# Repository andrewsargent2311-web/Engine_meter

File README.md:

# Engine Meter (RPMuffin)

A small, battery-powered engine monitor for a paramotor. It measures **RPM**, **CHT** and **EGT**, and sends them over **Bluetooth LE** as NMEA-style sentences to [Gaggle](https://www.gaggle.aero/) or the `paraglide_vario_ESP32` flight computer. It also reports its own battery percentage.

It was designed and tested on a **Moster 185** (single-cylinder two-stroke), but it should work on any engine with a spark-ignition lead and a thermocouple-instrumented head or exhaust.

| | |
|---|---|
| **MCU** | nice!nano (nRF52840) |
| **RPM** | Inductive pickup (2 wraps on the HT lead) → LMV331 comparator → interrupt |
| **Temperature** | 2 × MAX31856 thermocouple amplifiers (CHT + EGT), K-type as shipped |
| **Radio** | BLE, Nordic UART Service, advertises as `ParaEngineMeter` |
| **Update rate** | 5 Hz |
| **Power** | 1000 mAh single-cell LiPo, JST-PH 2.0 mm, charged over USB-C |
| **PCB** | 2 layers, 1.6 mm, about 50.6 × 75.1 mm |
| **Case** | 3D printed (PLA), about 58.5 × 123.5 × 27 mm including mounting tabs |

---

## Repository layout

| Path | Contents |
|---|---|
| `Engine_meter/` | PlatformIO firmware project (open **this** folder in VS Code) |
| `Engine_meter/src/` | `main.cpp` (RPM, thermocouples, BLE) and `AuxSensors.cpp/.h` (battery gauge) |
| `Engine_meter/boards/` | Custom `nicenano` board definition and pin variant for PlatformIO |
| `Engine_monitor_V1/` | KiCad 10 project: schematic and PCB |
| `Engine_monitor_V1/Gerber files/` | Fabrication outputs: Gerbers, drill files, JLCPCB BOM, JLCPCB CPL, and `Engine_monitor_V1_order.zip` |
| `3D print files/` | Case and lid as STL, plus ready-sliced G-code for a Prusa MK3S |
| `Photos/` | Photos of the bare PCB and the finished unit |

---

## 1. Parts list

### Parts on the PCB (SMD, 0805 unless noted)

These are the parts in `Engine_monitor_V1_BOM_JLCPCB.xlsx`, and they can be assembled by JLCPCB.

| Qty | Value | Designators | Notes |
|---|---|---|---|
| 4 | 10 nF 50 V X7R | C1, C3, C9, C10 | Thermocouple input filtering |
| 7 | 100 nF 50 V X7R | C2, C4, C5, C8, C11, C12, C14 | Decoupling; C8 filters the comparator reference |
| 2 | 10 µF 25 V X5R | C6, C13 | 3.3 V bulk decoupling |
| 4 | 100 Ω 1 % | R1, R2, R11, R12 | Thermocouple input series resistors |
| 5 | 10 kΩ 1 % | R4, R5, R7, R8, R9 | R4/R5 chip-select pull-ups, R7/R8 comparator reference divider, R9 comparator output pull-up |
| 1 | **150 kΩ** 1 % | R10 | RPM input series resistor. See the note below |
| 1 | 1 MΩ 1 % | R13 | Comparator hysteresis (positive feedback) |
| 1 | 220 kΩ 1 % | R14 | RPM input divider to GND |
| 2 | 1N5819HW-7-F Schottky, SOD-123 | D9, D10 | RPM input clamps (to 3.3 V and to GND) |
| 1 | LMV331IDBVR, SOT-23-5 | U2 | Single comparator |
| 2 | MAX31856MUD+, TSSOP-14 | U3, U4 | U3 = **CHT**, U4 = **EGT** |

> **R10 value:** the production design uses **150 kΩ**. It was originally 22 kΩ, which was too sensitive to pick up noise on the ignition lead, so it was increased. Use 150 kΩ.
>
> **D9/D10 in the JLCPCB BOM** are marked "consigned" (you supply them). Either supply 1N5819HW-7-F parts yourself, or pick an in-stock SOD-123 Schottky at order time.

### Parts you add by hand (through-hole / modules)

| Ref | Part | Purpose |
|---|---|---|
| U1 | **nice!nano** (v2 or compatible, nRF52840), 2 × 12-pin headers or castellated solder | MCU, BLE radio, LiPo charger |
| BT1 | JST-PH 2.0 mm 2-pin horizontal header (S2B-PH-K) | Battery connector |
| J2 | 2-pin screw terminal, 3.81 mm pitch (Phoenix MC 1,5/2-G-3.81 footprint) | **Power switch** (in series with the battery) |
| X1 | 2-pin screw terminal, 3.5 mm pitch | **CHT** thermocouple input |
| X2 | 2-pin screw terminal, 3.5 mm pitch | **EGT** thermocouple input |
| J1 | 1-pin 2.54 mm header (or a wire soldered straight in) | RPM pickup input |

### Other items

- **Battery:** 1000 mAh single-cell LiPo with a **2 mm JST-PH** connector (ideally with a built-in protection circuit).
- **Power switch:** any small SPST switch rated for a few hundred mA, wired to J2.
- **Thermocouples:** two K-type probes, one for CHT (for example a spark-plug washer or bolt-on type) and one for EGT (exhaust probe). Use proper thermocouple wire or a compensated extension.
- **RPM pickup wire:** a short length of insulated hookup wire.
- **Fasteners:** 4 small self-tapping screws for the lid (see section 5), plus zip ties or straps for mounting.
- USB-C cable for programming and charging.

---

## 2. Order and build the PCB

1. Go to JLCPCB and upload `Engine_monitor_V1/Gerber files/Engine_monitor_V1_order.zip`.
2. Settings: **2 layers, 1.6 mm** thickness. The board is about 50.6 × 75.1 mm.
3. **Bare board:** order the PCB only and hand-solder everything.
4. **Assembled:** tick *PCB Assembly*, then upload `Engine_monitor_V1_BOM_JLCPCB.xlsx` and `Engine_monitor_V1_CPL_JLCPCB.csv`. The BOM has no LCSC part numbers, so match each line to a stocked part in the JLCPCB parts picker (see the part table above). Only the SMD parts on the top side are assembled. You add the nice!nano, terminals, header and JST connector yourself.

### Hand-soldering order (if building from a bare board)

The two MAX31856 chips are TSSOP-14, so the SMD parts are best done with flux, a fine tip and a magnifier.

1. U2, U3, U4 (the ICs). Check pin 1 orientation against the silkscreen.
2. The 0805 resistors and capacitors, then the two diodes D9/D10 (check the stripe against the silkscreen).
3. Terminal blocks X1, X2, J2 and the JST connector BT1.
4. J1.
5. Finally the nice!nano. Either solder header pins or solder it directly. Keep the USB-C end of the board towards the board edge as shown in the silkscreen.

---

## 3. How the hardware works

### Pin map

The firmware uses software (bit-banged) SPI, so the two MAX31856s share one bus with separate chip-selects.

| Signal | nice!nano GPIO | Firmware pin number |
|---|---|---|
| MAX31856 SDO → MCU (MISO) | P1.00 | 32 |
| MAX31856 SDI ← MCU (MOSI) | P1.13 | 45 |
| SCK | P1.15 | 47 |
| CS for **CHT** (U3) | P0.11 | 11 |
| CS for **EGT** (U4) | P1.04 | 36 |
| RPM comparator output | P1.11 | 43 |

Pin numbers follow the Adafruit nRF52 core convention: P0.xx → xx, P1.xx → 32 + xx.

### RPM input

- The pickup wire goes to **J1**. It passes through **R10 (150 kΩ)** into a divider with **R14 (220 kΩ)**, giving roughly 0.6 × the input voltage. **D10** clamps to GND and **D9** clamps to 3.3 V to protect the comparator.
- **U2 (LMV331)** compares that signal with a **1.65 V** reference made by R7/R8 and filtered by C8. As a rough guide, the pickup needs to swing above about **2.8 V** at J1 to trigger.
- **R13 (1 MΩ)** feeds the output back to the input for hysteresis. **R9 (10 kΩ)** pulls the open-collector output up to 3.3 V.
- The nRF52840 counts the rising edges on an interrupt.

### Thermocouple input

Each channel copies the Adafruit MAX31856 breakout design: 100 Ω series resistors on the thermocouple inputs, 10 nF / 100 nF filtering, and a 10 kΩ pull-up on each chip-select. **X1 = CHT (U3)** and **X2 = EGT (U4)**.

Polarity matters. If a reading falls when you warm the probe, swap the two wires. The firmware sets **type K** for both channels, but the MAX31856 supports B, E, J, K, N, R, S and T. To change it, edit the two `setThermocoupleType(...)` lines in `setup()` in `Engine_meter/src/main.cpp`.

### Power

- The battery connects to **BT1**. BT1 pin 1 is battery **+** and pin 2 is **GND**.
- **BT1 + goes to J2 (the switch), and the other side of the switch goes to the nice!nano's battery-in pin** (pin 26, marked BATIN/RAW on the board). So the battery is only connected to the nice!nano while the switch is **on**. Charge with the switch on.
- Charging happens through the nice!nano's USB-C port. It charges at roughly **100 mA**, so a flat 1000 mAh pack takes about **10 hours**.
- The nice!nano's regulator provides the 3.3 V rail for the comparator and both MAX31856s.

> ⚠️ **Check battery polarity before the first power-up.** JST-PH LiPo packs from different suppliers are wired in different orders, and a reversed pack can destroy the nice!nano. Use a multimeter on the pack connector, and compare it with BT1 (pin 1 = +, pin 2 = GND) on the PCB. If it is reversed, re-pin the connector on the battery lead.

---

## 4. Firmware

The firmware is a PlatformIO project in `Engine_meter/`.

### Build and upload

1. Install [VS Code](https://code.visualstudio.com/) and the **PlatformIO IDE** extension.
2. **File → Open Folder…** and choose the `Engine_meter` folder (not the repo root).
3. PlatformIO downloads the `nordicnrf52` platform and the libraries (Adafruit MAX31856, BusIO and TinyUSB) on first build.
4. Build, then upload with the nice!nano plugged in over USB-C. PlatformIO will try to reset it into the bootloader automatically. If the upload hangs, **double-tap the reset button** and upload again. The bootloader appears as its own COM port (`VID_239A&PID_00B3`), and the upload must target that port.
5. For debug output, open the running firmware's serial port at **115200 baud**. It prints a line every 200 ms with RPM, raw RPM, pulse and reject counts, EGT, CHT and battery %.

The `nicenano` board definition in `boards/` comes from [ICantMakeThings/Nicenano-NRF52-Supermini-PlatformIO-Support](https://github.com/ICantMakeThings/Nicenano-NRF52-Supermini-PlatformIO-Support) via [bertrik/nicenano-example](https://github.com/bertrik/nicenano-example).

### Settings you may want to change (`Engine_meter/src/main.cpp`)

| Setting | Default | Meaning |
|---|---|---|
| `PULSES_PER_REV` | `1.0` | Spark pulses per crank revolution. Correct for a single-cylinder two-stroke such as the Moster 185. If the reading is double or half what you expect, change this |
| `RPM_TIMEOUT_MS` | `1500` | No pulse for this long → RPM reports 0 |
| `RPM_WINDOW_MS` | `5000` | RPM averaging window |
| `RPM_FAST_ATTACK` / `RPM_FAST_WINDOW_MS` / `RPM_FAST_THRESHOLD` | `1` / `1000` / `0.10` | Use a 1 s window when it differs from the 5 s average by more than 10 % |
| `RPM_ROUND_TO` / `RPM_HYST` | `10` / `7.0` | Displayed RPM is rounded to 10 RPM with 7 RPM hysteresis |
| `RPM_MIN_LOCKOUT_US` | `5000` | Ignores edges closer together than this (ringing rejection). It adapts to 40 % of the last period above about 600 RPM |
| `SEND_PEMBAT` | `1` | Set to `0` to stop sending the proprietary battery sentence |
| `RPM_DEBUG_EDGES` | `0` | Set to `1` to print raw edge intervals when diagnosing pickup noise |

### BLE output

The device advertises as **`ParaEngineMeter`** and exposes the Nordic UART Service. Each message is an ASCII sentence with an XOR checksum and CRLF line ending.

```
$EMS,<pressure>,<fuelFlow>,<fuelRemaining>,<fuelUsed>,<ambientTemp>,<CHT>,<EGT>,<waterTemp>,<RPM>*HH
$PEMBAT,<percent>*HH
```

- Unused `EMS` fields are filled with `999999` (pressure), `9999` (fuel fields) or `99` (temperatures).
- **CHT and EGT** are in °C × 100, clamped to −300..1500 °C. A value of `99` means unavailable (sensor fault).
- **RPM** is sent × 100. `0` is a valid stopped-engine reading.
- **`$PEMBAT`** is battery percentage, 0–100, estimated from the nRF52840's internal supply-voltage ADC and a single-cell LiPo curve. It is approximate. It reads high while charging and sags under load.

Example: RPM 3100, CHT 180.0 °C, EGT 550.0 °C:

```
$EMS,999999,9999,9999,9999,99,18000,55000,99,310000*7C
```

**Gaggle:** add the meter under *Profile → Equipment → Bluetooth Devices*. Gaggle must receive a real supported reading within about 35 seconds.

**paraglide_vario_ESP32:** select `ParaEngineMeter` in the vario's Bluetooth scan list.

---

## 5. 3D printed case

The case and lid are in `3D print files/`.

| File | Print time (Prusa MK3S, 0.15 mm, PLA) |
|---|---|
| `Engine meter case.stl` | 5 h 18 min |
| `Engine meter lid.stl` | 1 h 44 min |

Ready-sliced G-code for a Prusa MK3S is included. For another printer, slice the STLs yourself, 0.15 mm layers in PLA or similar (PETG is a better choice for a hot, sunny harness).

- The **PCB sits in the case** and the **battery sits in the lid**, as in the photo above.
- The lid is held on by **4 small self-tapping screws** into the corner holes (the lid has pilot holes at about 2 mm).
- The **mounting tabs** on each side have slots (about 2.5 × 4.5 mm) for zip ties or straps.
- The case was designed in Onshape.

---

## 6. Wiring it to the engine

### RPM pickup

1. Take a length of insulated wire. Solder one end to **J1**.
2. Wrap the other end **2 turns around the ignition (HT) lead**, close to the spark plug cap. Do not connect it to anything else. The signal is picked up by coupling alone.
3. Secure the wrap with heat-shrink or tape, and keep the lead clear of the exhaust and moving parts.

If RPM is wrong: no reading means add a turn, and spurious readings mean remove a turn or move the wrap further from the plug. The `rejects` counter in the serial output shows how many noise edges are being filtered. The reading is also wrong if `PULSES_PER_REV` doesn't match your engine.

### Thermocouples

- **CHT probe → X1**, **EGT probe → X2**.
- Keep thermocouple wires away from the ignition lead and coil.

### Power

Connect a switch to **J2**, plug the battery into **BT1** (after checking polarity), and charge through the nice!nano's USB-C port.

---

## 7. First power-up checklist

1. Check the 3.3 V rail on the board with a meter before fitting the nice!nano (if you soldered it in a socket).
2. Plug the battery in, switch on, and confirm the nice!nano powers up.
3. Connect USB, open the serial monitor at 115200 baud, and confirm you see `[BOOT] Engine meter ready, advertising as ParaEngineMeter`.
4. With nothing connected, thermocouple channels will show a fault. With a probe attached you should see room temperature. Warm the probe and check that the reading rises.
5. Check the `BAT=` value is sensible for the pack voltage.
6. With the engine running, check the RPM against a known reference such as a handheld tachometer.
7. Connect from Gaggle or the vario (or a generic BLE app such as nRF Connect) and confirm `$EMS` sentences arrive.

---

## License

This project is open source under the **GNU General Public License v3.0**. See [`LICENSE`](LICENSE) for the full text. It covers the firmware, PCB design files, case models and documentation in this repository. You are free to build, modify and share it, and if you distribute a modified version you must release your changes under the same license.

Third-party files keep their own licenses and notices (see Credits below).

## Credits

- Thermocouple front end based on the [Adafruit MAX31856 breakout](https://www.adafruit.com/product/3263).
- nice!nano board support from ICantMakeThings and bertrik (linked above).
- Firmware uses the Adafruit nRF52 Arduino core (Bluefruit) and the Adafruit MAX31856 library.

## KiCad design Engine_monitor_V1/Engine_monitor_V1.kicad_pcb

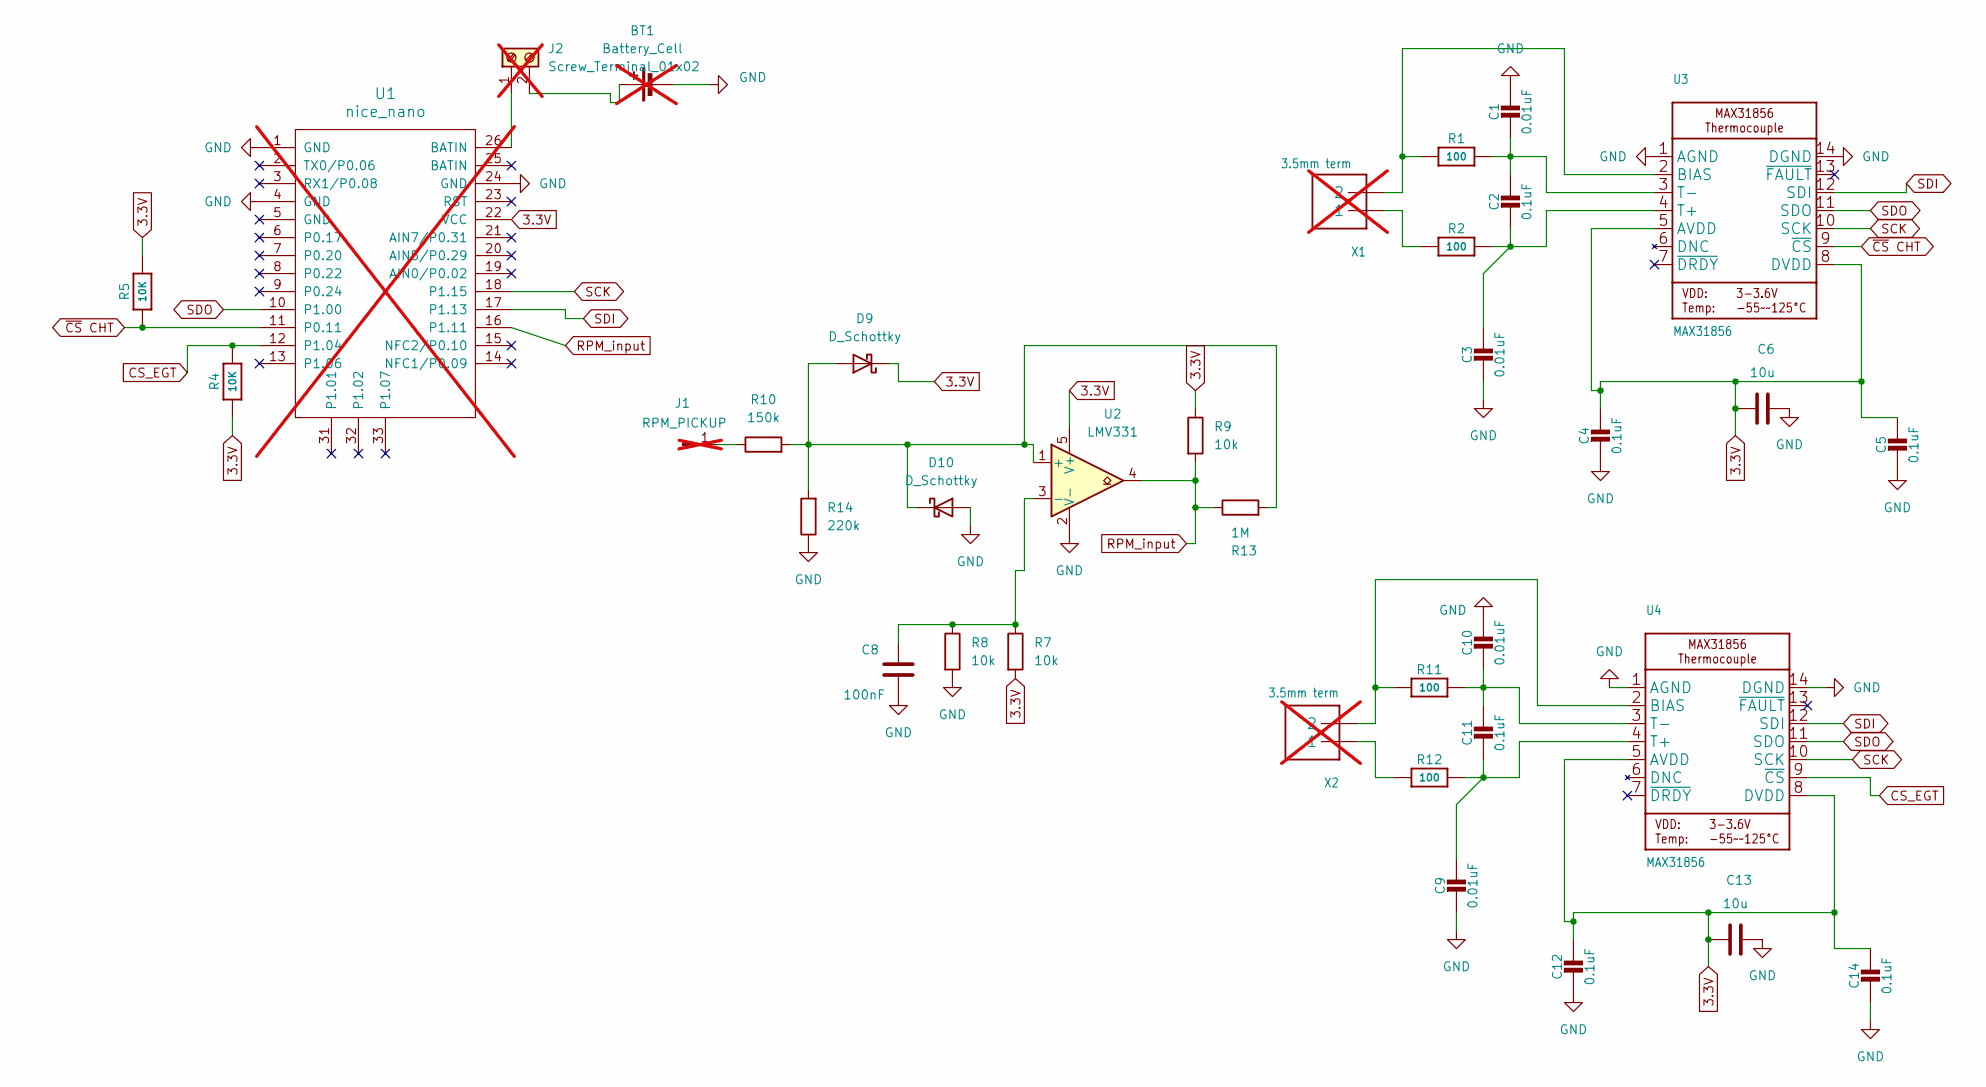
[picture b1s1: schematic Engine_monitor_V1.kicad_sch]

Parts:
BT1: Battery_Cell; JST_PH_S2B-PH-K_1x02_P2.00mm_Horizontal; not fitted
C1, C10: 0.01uF; 0805_10MGAP
C2, C4, C5, C11, C12, C14: 0.1uF; 0805-NO
C3, C9: 0.01uF; 0805-NO
C6, C13: 10u; C_0805_2012Metric
C8: 100nF; C_0805_2012Metric
D9, D10: D_Schottky; D_SOD-123
J1: RPM_PICKUP; PinHeader_1x01_P2.54mm_Vertical; not fitted
J2: Screw_Terminal_01x02; PhoenixContact_MC_1,5_2-G-3.81_1x02_P3.81mm_Horizontal; not fitted
R1, R2, R11, R12: 100; 0805-NO
R4, R5: 10K; R_0805_2012Metric_Pad1.20x1.40mm_HandSolder
R7, R8, R9: 10k; R_0805_2012Metric
R10: 150k; R_0805_2012Metric
R13: 1M; R_0805_2012Metric
R14: 220k; R_0805_2012Metric
U1: nice_nano; not fitted
U2: LMV331; SOT-23-5
U3, U4: MAX31856; TSSOP14
X1, X2: 3.5mm term; TERMBLOCK_1X2-3.5MM; not fitted

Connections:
3.3V: C4.1, C5.1, C6.2, C12.1, C13.2, C14.1, D9.1 (K), R4.1, R5.2, R7.2, R9.1, U1.22 (VCC), U2.5 (V+), U3.5 (AVDD), U3.8 (DVDD), U4.5 (AVDD), U4.8 (DVDD)
CS_EGT: R4.2, U1.12 (P1.04), U4.9 (~CS)
GND: BT1.2 (-), C1.1, C3.2, C4.2, C5.2, C6.1, C8.2, C9.2, C10.1, C12.2, C13.1, C14.2, D10.2 (A), R8.2, R14.1, U1.1 (GND), U1.4 (GND), U1.24 (GND), U2.2 (V-), U3.1 (AGND), U3.14 (DGND), U4.1 (AGND), U4.14 (DGND)
unnamed: BT1.1 (+), J2.2
unnamed: D9.2 (A), D10.1 (K), R10.2, R13.2, R14.2, U2.1 (+)
unnamed: J1.1 (Pin_1_1), R10.1
unnamed: J2.1, U1.26 (BATIN)
unnamed: R2.1, X1.1
unnamed: R12.1, X2.1
unnamed: C8.1, R7.1, R8.1, U2.3 (-)
unnamed: R1.1, U3.2 (BIAS), X1.2
unnamed: C2.2, C3.1, R2.2, U3.4 (T+)
unnamed: C1.2, C2.1, R1.2, U3.3 (T-)
unnamed: R11.1, U4.2 (BIAS), X2.2
unnamed: C9.1, C11.2, R12.2, U4.4 (T+)
unnamed: C10.2, C11.1, R11.2, U4.3 (T-)
RPM_input: R9.2, R13.1, U1.16 (P1.11), U2.4
SCK: U1.18 (P1.15), U3.10 (SCK), U4.10 (SCK)
SDI: U1.17 (P1.13), U3.12 (SDI), U4.12 (SDI)
SDO: U1.10 (P1.00), U3.11 (SDO), U4.11 (SDO)
~CS CHT: R5.1, U1.11 (P0.11), U3.9 (~CS)

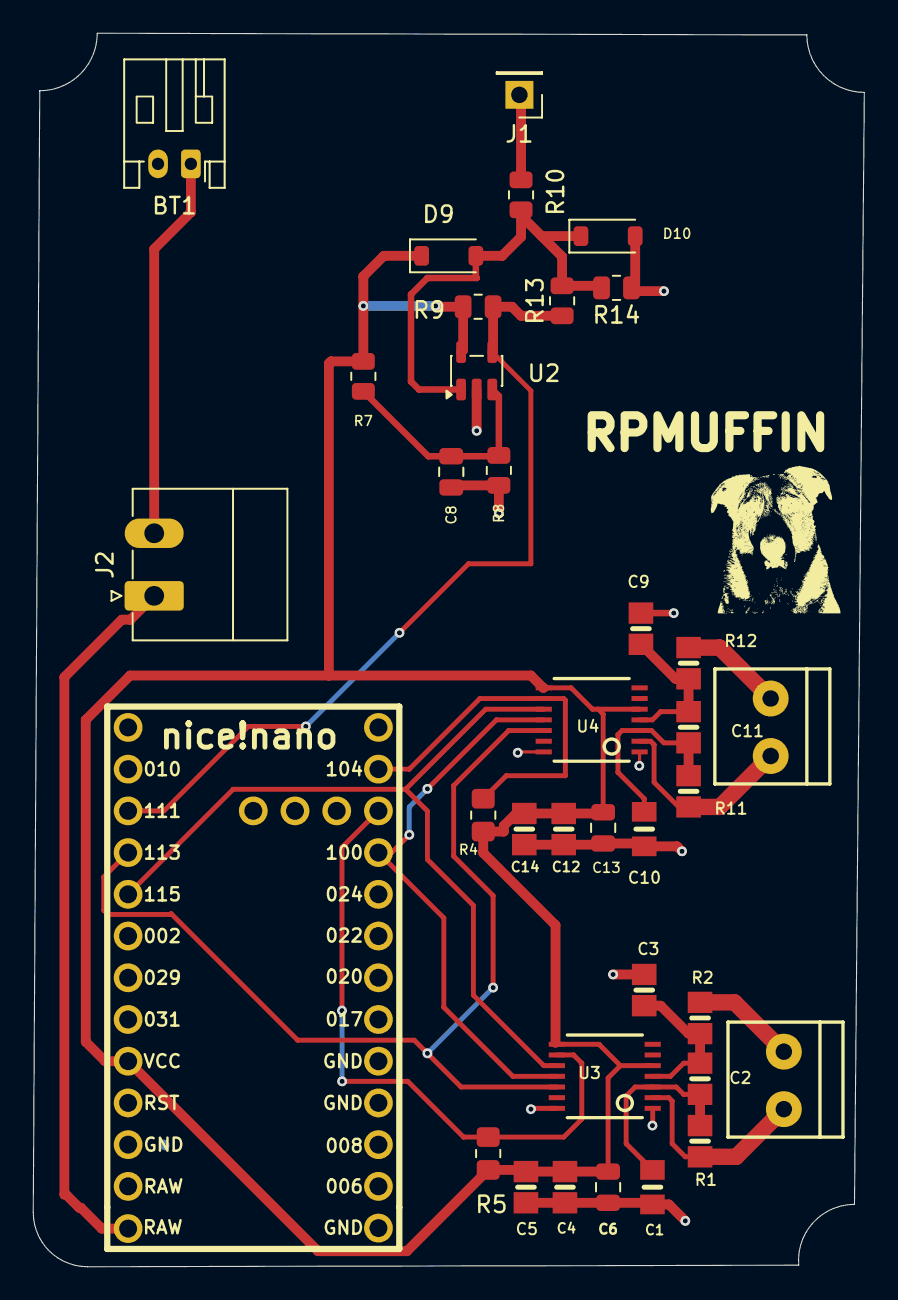
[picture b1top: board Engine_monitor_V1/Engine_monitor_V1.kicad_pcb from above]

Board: 2 copper layers, 50.6 x 75.1 mm, 36 parts (0 on the bottom side), 21 nets.

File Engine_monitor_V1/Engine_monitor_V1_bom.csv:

"Reference","Qty","Value","DNP","Exclude from BOM","Exclude from Board","Footprint","Datasheet"
"C1,C10","2","0.01uF","","","","Adafruit MAX31856:0805_10MGAP",""
"C2,C4,C5,C11,C12,C14","6","0.1uF","","","","Adafruit MAX31856:0805-NO",""
"C3,C9","2","0.01uF","","","","Adafruit MAX31856:0805-NO",""
"C6,C13","2","10u","","","","Capacitor_SMD:C_0805_2012Metric",""
"C8","1","100nF","","","","Capacitor_SMD:C_0805_2012Metric",""
"D9,D10","2","D_Schottky","","","","Diode_SMD:D_SOD-123",""
"R1,R2,R11,R12","4","100","","","","Adafruit MAX31856:0805-NO",""
"R4,R5","2","10K","","","","Resistor_SMD:R_0805_2012Metric_Pad1.20x1.40mm_HandSolder",""
"R7,R8,R9","3","10k","","","","Resistor_SMD:R_0805_2012Metric",""
"R10","1","150k","","","","Resistor_SMD:R_0805_2012Metric",""
"R13","1","1M","","","","Resistor_SMD:R_0805_2012Metric",""
"R14","1","220k","","","","Resistor_SMD:R_0805_2012Metric",""
"U2","1","LMV331","","","","Package_TO_SOT_SMD:SOT-23-5","http://www.ti.com/lit/ds/symlink/lmv331.pdf"
"U3,U4","2","MAX31856","","","","Adafruit MAX31856:TSSOP14",""

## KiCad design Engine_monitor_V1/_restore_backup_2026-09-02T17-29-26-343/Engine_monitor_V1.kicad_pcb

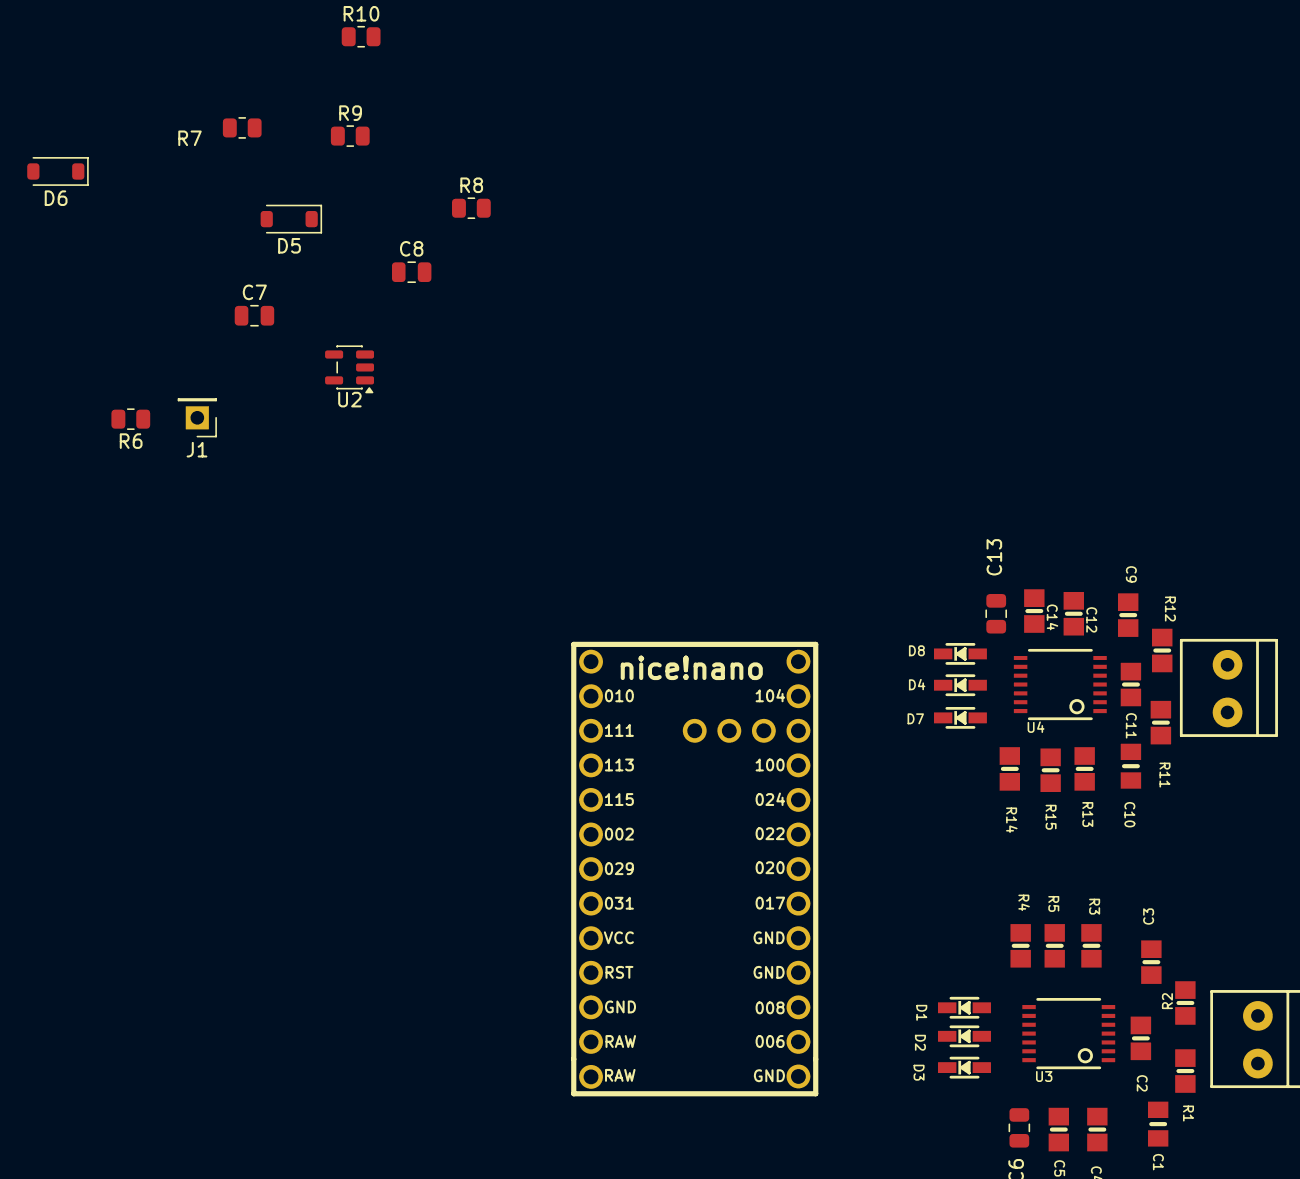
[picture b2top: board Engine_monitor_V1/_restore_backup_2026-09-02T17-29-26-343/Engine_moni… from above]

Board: 2 copper layers, 44 parts (0 on the bottom side), 22 nets, no tracks yet.

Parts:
C1, C10: 0.01uF; 0805_10MGAP
C2, C4, C5, C11, C12, C14: 0.1uF; 0805-NO
C3, C9: 0.01uF; 0805-NO
C6, C13: 10u; C_0805_2012Metric
C7: 10nF; C_0805_2012Metric
C8: 100nF; C_0805_2012Metric
D1, D2, D3, D4, D7, D8: 1N4148; SOD-323
D5, D6: BAT54W; D_SOD-123
J1: RPM_PICKUP; PinHeader_1x01_P2.54mm_Vertical
R1, R2, R11, R12: 100; 0805-NO
R3, R4, R5, R13, R14, R15: 10K; 0805-NO
R6: 22k; R_0805_2012Metric
R7, R8, R9: 10k; R_0805_2012Metric
R10: 1M; R_0805_2012Metric
U1: nice_nano
U2: LMV331; SOT-23-5
U3, U4: MAX31856; TSSOP14
X1, X2: 3.5mm term; TERMBLOCK_1X2-3.5MM

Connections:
3.3V: C4.1, C5.1, C6.2, C12.1, C13.2, C14.1, R3.2, R4.2, R5.2, R7.2, R9.1, R13.2, R14.2, R15.2, U1.22 (VCC), U2.5 (V+), U3.5 (AVDD), U3.8 (DVDD), U4.5 (AVDD), U4.8 (DVDD)
CS_EGT: D8.C, U1.12 (P1.04)
GND: C1.1, C3.2, C4.2, C5.2, C6.1, C7.2, C8.2, C9.2, C10.1, C12.2, C13.1, C14.2, D6.1 (A_1), R8.2, U1.1 (GND), U1.4 (GND), U1.24 (GND), U2.2 (V-), U3.1 (AGND), U3.14 (DGND), U4.1 (AGND), U4.14 (DGND)
unnamed: C7.1, D5.1 (A_1), R6.2, R10.2, U2.1 (+)
unnamed: J1.1 (Pin_1_1), R6.1
unnamed: R2.1, X1.1
unnamed: R12.1, X2.1
unnamed: C8.1, R7.1, R8.1, U2.3 (-)
unnamed: D2.A, R4.1, U3.10 (SCK)
unnamed: D3.A, R3.1, U3.12 (SDI)
unnamed: D1.A, R5.1, U3.9 (~CS)
unnamed: D4.A, R14.1, U4.10 (SCK)
unnamed: D7.A, R13.1, U4.12 (SDI)
unnamed: D8.A, R15.1, U4.9 (~CS)
RPM_input: R9.2, R10.1, U1.16 (P1.11), U2.4
SCK: D2.C, D4.C, U1.8 (P0.22)
SDI: D3.C, D7.C, U1.9 (P0.24)
SDO: U1.10 (P1.00), U3.11 (SDO), U4.11 (SDO)
T+: C2.2, C3.1, C9.1, C11.2, R2.2, R12.2, U3.4 (T+), U4.4 (T+)
T-: C1.2, C2.1, C10.2, C11.1, R1.2, R11.2, U3.3 (T-), U4.3 (T-)
THERM-: R1.1, R11.1, U3.2 (BIAS), U4.2 (BIAS), X1.2, X2.2
~CS CHT: D1.C, U1.11 (P0.11)

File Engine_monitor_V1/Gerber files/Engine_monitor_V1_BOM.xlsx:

Item # | Designator | Qty | Value / Description | Package / Footprint | Manufacturer | Manufacturer Part # | Type | Notes
1.0 | C1,C3,C9,C10 | 4.0 | 10nF, 50V, X7R, ±10% | 0805 | Samsung | CL21B103KBANNNC | SMD | MAX31856 filter caps
2.0 | C2,C4,C5,C8,C11,C12,C14 | 7.0 | 100nF, 50V, X7R, ±10% | 0805 | Samsung | CL21B104KBCNNNC | SMD | 0.1uF = 100nF, merged
3.0 | C6,C13 | 2.0 | 10uF, 25V, X5R, ±10% | 0805 | Samsung | CL21A106KAYNNNE | SMD
4.0 | R1,R2,R11,R12 | 4.0 | 100R, 1%, 1/8W | 0805 | Yageo | RC0805FR-07100RL | SMD
5.0 | R4,R5,R7,R8,R9 | 5.0 | 10k, 1%, 1/8W | 0805 | Yageo | RC0805FR-0710KL | SMD | R4/R5 '10K' and R7-R9 '10k' merged
6.0 | R10 | 1.0 | 150k, 1%, 1/8W | 0805 | Yageo | RC0805FR-07150KL | SMD
7.0 | R13 | 1.0 | 1M, 1%, 1/8W | 0805 | Yageo | RC0805FR-071ML | SMD
8.0 | R14 | 1.0 | 220k, 1%, 1/8W | 0805 | Yageo | RC0805FR-07220KL | SMD
9.0 | D9,D10 | 2.0 | 1N5819HW-7-F, Schottky, 40V 1A | SOD-123 | Diodes Inc. | 1N5819HW-7-F | SMD
10.0 | U2 | 1.0 | LMV331 single comparator | SOT-23-5 | Texas Instruments | LMV331IDBVR | SMD
11.0 | U3,U4 | 2.0 | MAX31856 thermocouple-to-digital converter | TSSOP-14 | Analog Devices (Maxim) | MAX31856MUD+ | SMD

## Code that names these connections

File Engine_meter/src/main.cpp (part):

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// ---------------------------------------------------------------------
// PINS (from schematic global labels)
// ---------------------------------------------------------------------
#define PIN_SDO     32   // P1.00 -- MAX31856 SDO  -> MCU MISO (shared bus)
#define PIN_CS_CHT  11   // P0.11 -- MAX31856 #2 (CHT) chip select
#define PIN_CS_EGT  36   // P1.04 -- MAX31856 #1 (EGT) chip select
#define PIN_SCK     47   // P1.15 -- shared SPI clock
#define PIN_SDI     45   // P1.13 -- MCU MOSI -> MAX31856 SDI (shared bus)
#define PIN_RPM     43   // P1.11 -- comparator output (LMV331), pulled up by R9

// ---------------------------------------------------------------------
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
// ---------------------------------------------------------------------
// Thermocouple amps -- software SPI (bit-banged) so we can use the
// arbitrary GPIOs the board routes them on, sharing one SCK/SDI/SDO bus
// with separate chip-selects.
// ---------------------------------------------------------------------
Adafruit_MAX31856 maxEGT(PIN_CS_EGT, PIN_SDI, PIN_SDO, PIN_SCK);
Adafruit_MAX31856 maxCHT(PIN_CS_CHT, PIN_SDI, PIN_SDO, PIN_SCK);

// ---------------------------------------------------------------------
// RPM: raw pulse periods are captured in the ISR; accepted-pulse snapshots
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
